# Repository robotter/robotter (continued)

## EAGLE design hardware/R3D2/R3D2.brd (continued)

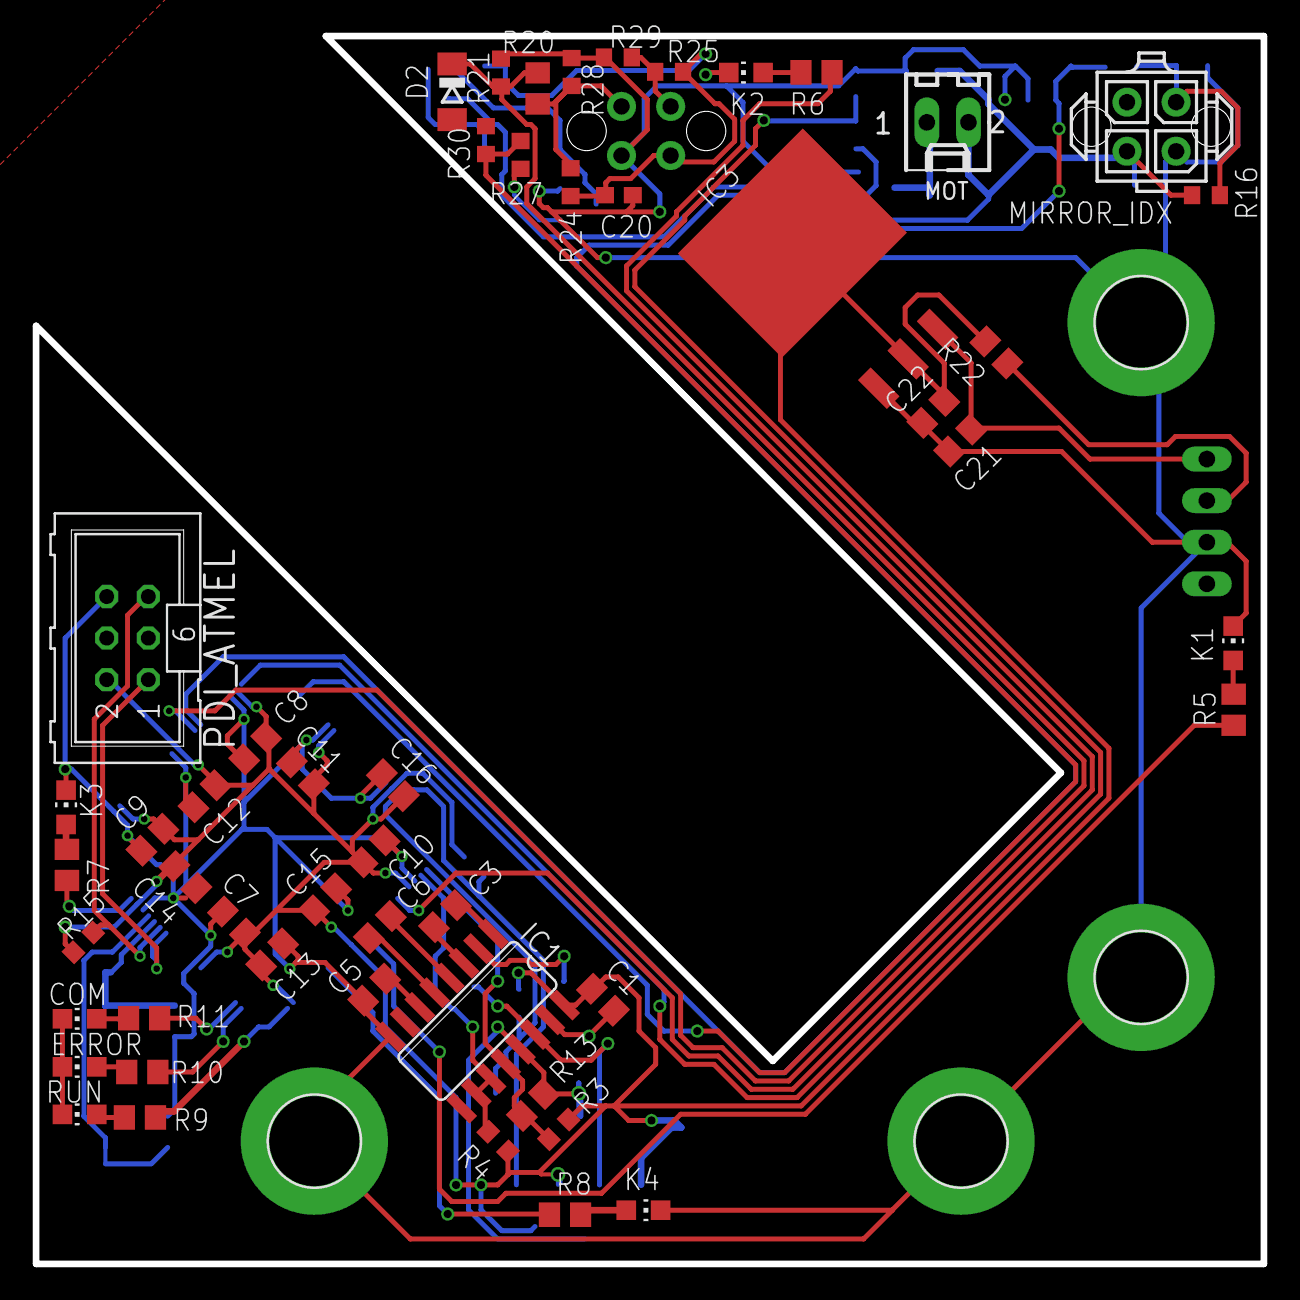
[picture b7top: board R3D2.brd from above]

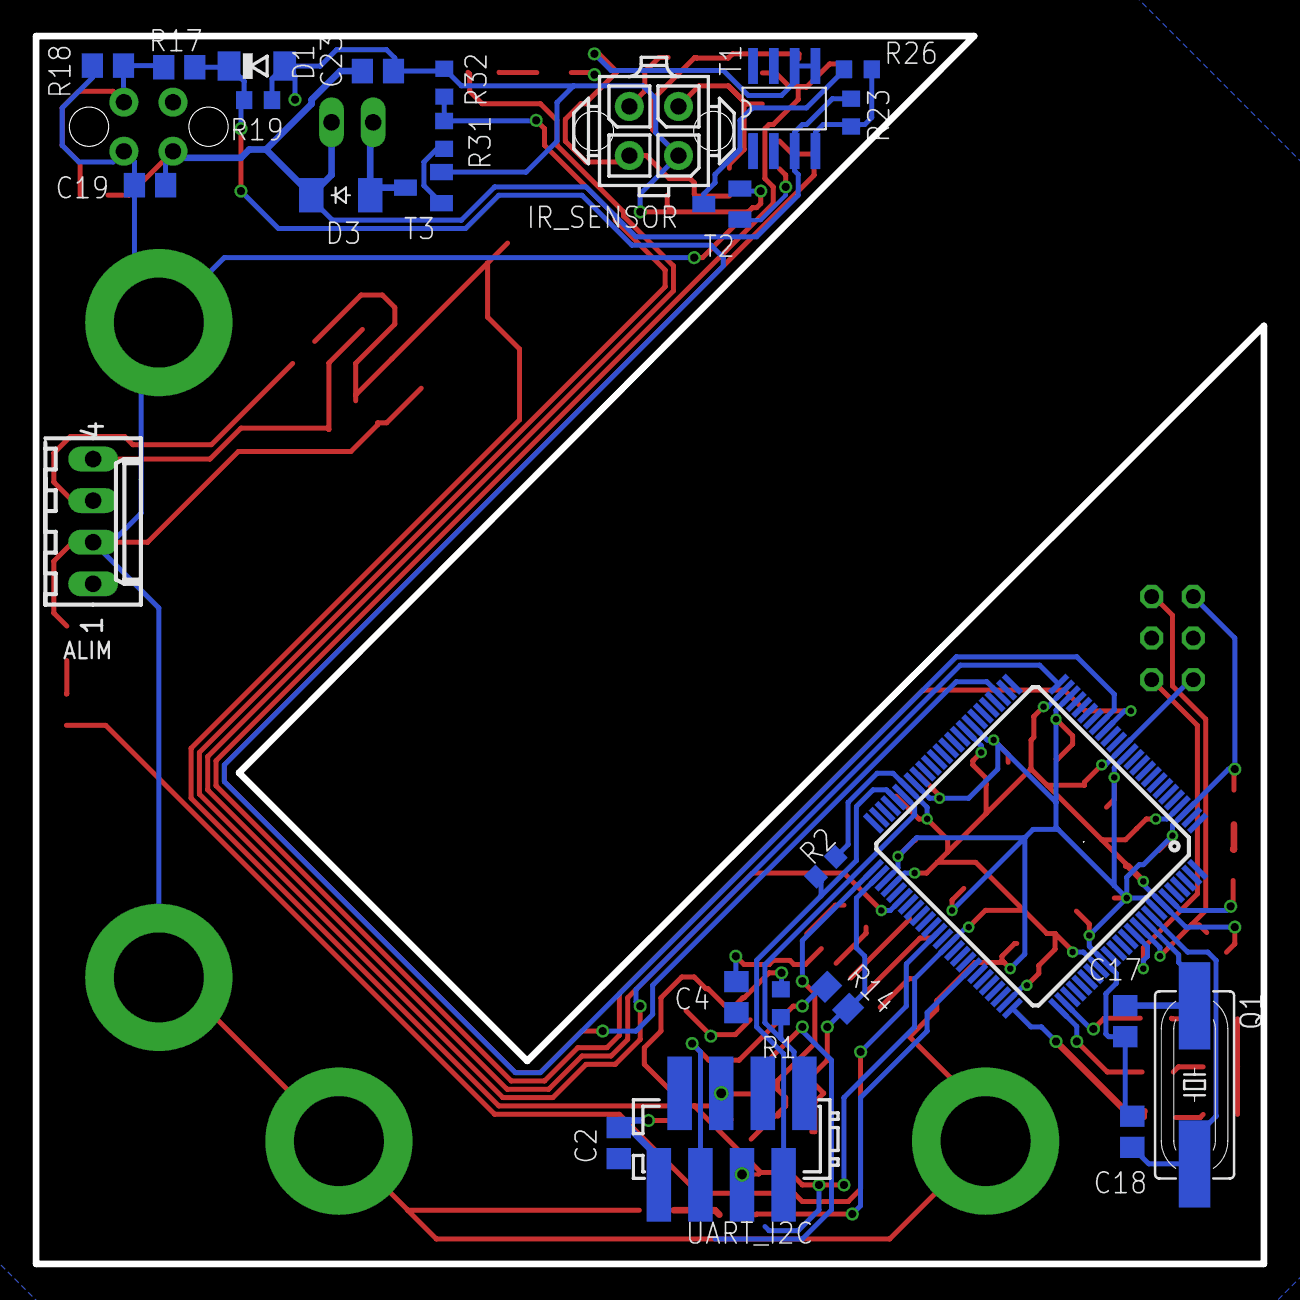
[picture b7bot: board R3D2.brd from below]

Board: 2 copper layers, 75.0 x 75.0 mm, 81 parts (26 on the bottom side), 48 nets.

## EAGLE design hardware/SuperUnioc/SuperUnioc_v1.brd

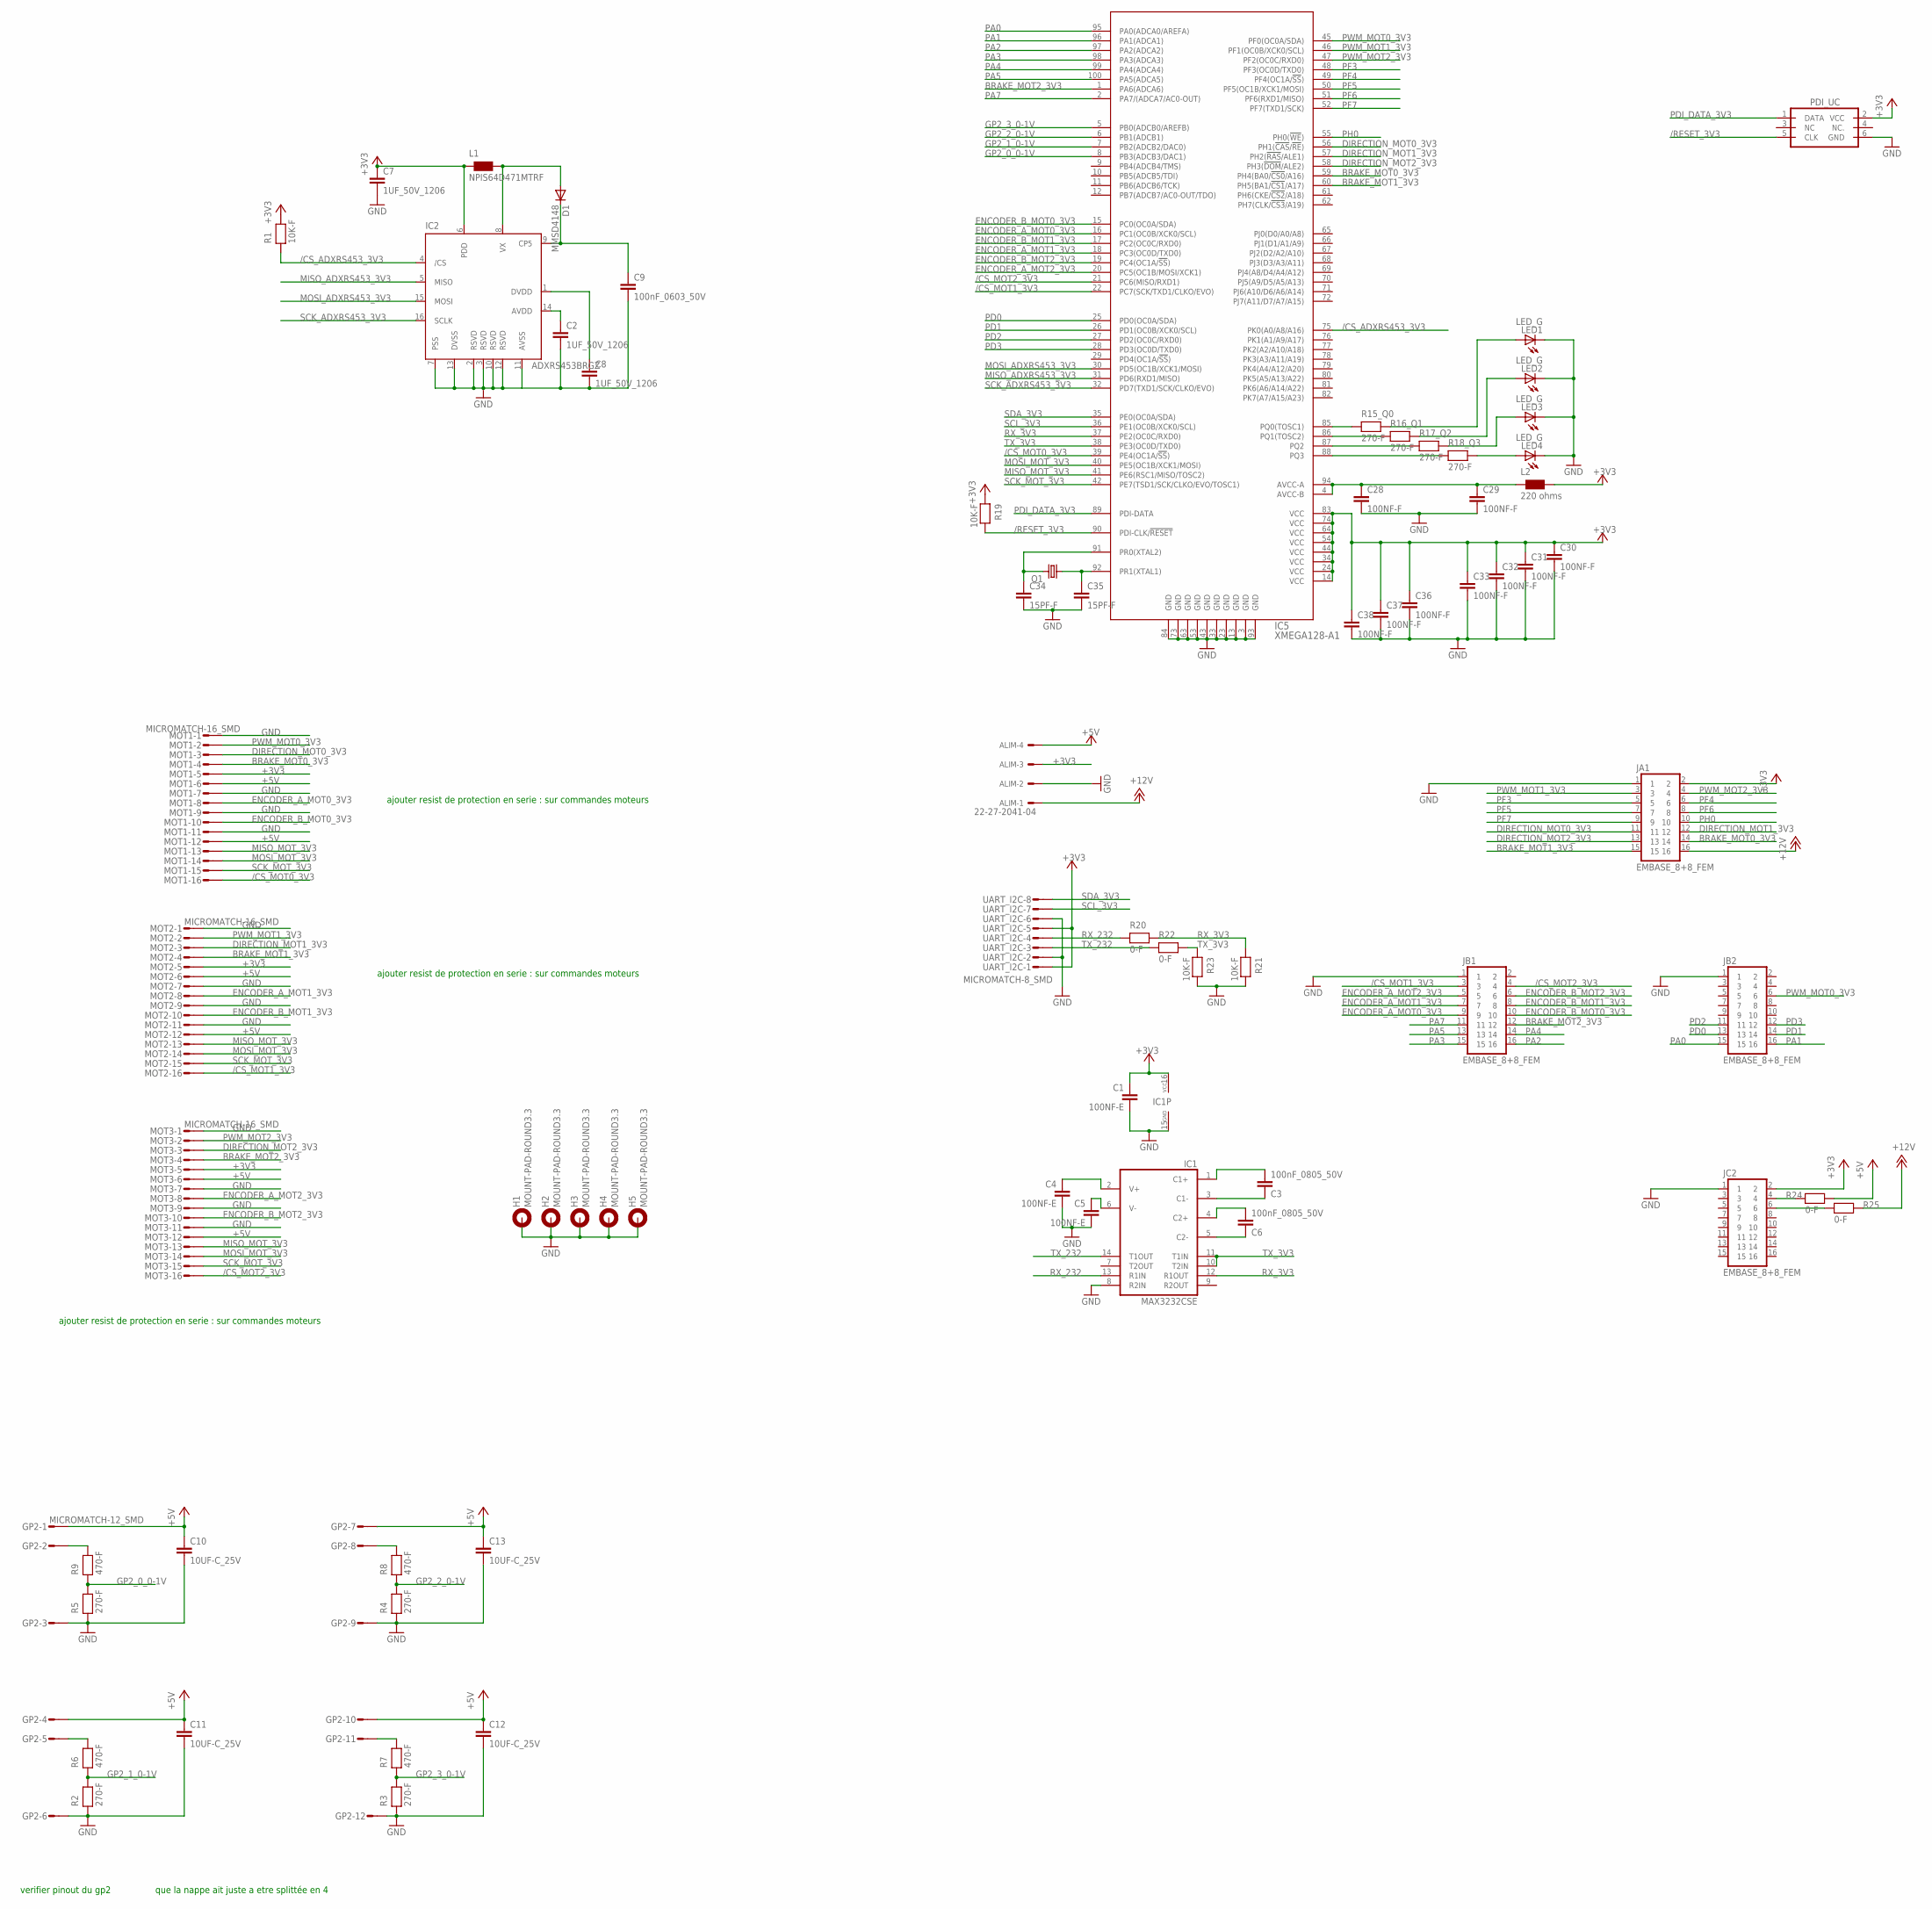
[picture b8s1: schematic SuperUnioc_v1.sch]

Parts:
ALIM: 22-27-2041-04; 6410-04
C1, C4, C5: 100NF-E; C0805
C2, C7, C8: 1UF_50V_1206; C1206
C3, C6: 100nF_0805_50V; C0805
C9: 100nF_0603_50V; C0603
C10, C11, C12, C13: 10UF-C_25V; C1210
C28, C29, C30, C31, C32, C33, C36, C37, C38: 100NF-F; C0603
C34, C35: 15PF-F; C0603
D1: MMSD4148; SOD123
GP2: MICROMATCH-12_SMD
H1, H2, H3, H4, H5: MOUNT-PAD-ROUND3.3; 3,3-PAD
IC1: MAX3232CSE; SO16
IC2: ADXRS453BRGZ; SO16_CAV
IC5: XMEGA128-A1; TQFP100
JA1: EMBASE_8+8_FEM
JB1, JB2: EMBASE_8+8_FEM
JC2: EMBASE_8+8_FEM
L1: NPIS64D471MTRF; NPSIS_D64
L2: 220 ohms; R0603
LED1, LED2, LED3, LED4: LED_G; CHIP-LED0805
MOT1, MOT2, MOT3: MICROMATCH-16_SMD
PDI_UC: PDI_ATMELL; ML6L
Q1: CRYSTAL_16MHZ_HC49UP; HC49UP
R1, R19, R21, R23: 10K-F; R0603
R2, R3, R4, R5, R15_Q0, R16_Q1, R17_Q2, R18_Q3: 270-F; R0603
R6, R7, R8, R9: 470-F; R0603
R20, R22, R24, R25: 0-F; R0603
UART_I2C: MICROMATCH-8_SMD

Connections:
+3V3: ALIM.3, C1.1, C7.1, C30.1, C31.1, C32.1, C33.1, C36.1, C37.1, C38.1, IC1.16 (VCC), IC2.6 (PDD), IC5.14 (VCC), IC5.24 (VCC), IC5.34 (VCC), IC5.44 (VCC), IC5.54 (VCC), IC5.64 (VCC), IC5.74 (VCC), IC5.83 (VCC), JA1.2, JC2.2, L1.1, L2.2, MOT1.5, MOT2.5, MOT3.5, PDI_UC.2 (VCC), R1.2, R19.1, UART_I2C.1, UART_I2C.5
+5V: ALIM.4, C10.1, C11.1, C12.1, C13.1, GP2.1, GP2.4, GP2.7, GP2.10, MOT1.6, MOT1.12, MOT2.6, MOT2.12, MOT3.6, MOT3.12, R24.2
+12V: ALIM.1, JA1.16, R25.2
/CS_ADXRS453_3V3: IC2.4 (/CS), IC5.75 (PK0(A0/A8/A16)), R1.1
/CS_MOT0_3V3: IC5.39 (PE4(OC1A/!SS!)), MOT1.16
/CS_MOT1_3V3: IC5.22 (PC7(SCK/TXD1/CLKO/EVO)), JB1.3, MOT2.16
/CS_MOT2_3V3: IC5.21 (PC6(MISO/RXD1)), JB1.4, MOT3.16
/RESET_3V3: IC5.90 (PDI-CLK/!RESET), PDI_UC.5 (CLK), R19.2
BRAKE_MOT0_3V3: IC5.59 (PH4(BA0/!CS0!/A16)), JA1.14, MOT1.4
BRAKE_MOT1_3V3: IC5.60 (PH5(BA1/!CS1!/A17)), JA1.15, MOT2.4
BRAKE_MOT2_3V3: IC5.1 (PA6(ADCA6)), JB1.12, MOT3.4
DIRECTION_MOT0_3V3: IC5.56 (PH1(!CAS!/!RE!)), JA1.11, MOT1.3
DIRECTION_MOT1_3V3: IC5.57 (PH2(!RAS!/ALE1)), JA1.12, MOT2.3
DIRECTION_MOT2_3V3: IC5.58 (PH3(!DOM!/ALE2)), JA1.13, MOT3.3
ENCODER_A_MOT0_3V3: IC5.16 (PC1(OC0B/XCK0/SCL)), JB1.9, MOT1.8
ENCODER_A_MOT1_3V3: IC5.18 (PC3(OC0D/TXD0)), JB1.7, MOT2.8
ENCODER_A_MOT2_3V3: IC5.20 (PC5(OC1B/MOSI/XCK1)), JB1.5, MOT3.8
ENCODER_B_MOT0_3V3: IC5.15 (PC0(OC0A/SDA)), JB1.10, MOT1.10
ENCODER_B_MOT1_3V3: IC5.17 (PC2(OC0C/RXD0)), JB1.8, MOT2.10
ENCODER_B_MOT2_3V3: IC5.19 (PC4(OC1A/!SS!)), JB1.6, MOT3.10
GND: ALIM.2, C1.2, C2.2, C4.2, C5.2, C7.2, C8.2, C9.2, C10.2, C11.2, C12.2, C13.2, C28.2, C29.2, C30.2, C31.2, C32.2, C33.2, C34.2, C35.2, C36.2, C37.2, C38.2, GP2.3, GP2.6, GP2.9, GP2.12, H1.B3,3, H2.B3,3, H3.B3,3, H4.B3,3, H5.B3,3, IC1.8 (R2IN), IC1.15 (GND), IC2.2 (RSVD), IC2.3 (RSVD), IC2.7 (PSS), IC2.10 (RSVD), IC2.11 (AVSS), IC2.12 (RSVD), IC2.13 (DVSS), IC5.3 (GND), IC5.13 (GND), IC5.23 (GND), IC5.33 (GND), IC5.43 (GND), IC5.53 (GND), IC5.63 (GND), IC5.73 (GND), IC5.84 (GND), IC5.93 (GND), JA1.1, JB1.1, JB2.1, JC2.1, LED1.C, LED2.C, LED3.C, LED4.C, MOT1.1, MOT1.7, MOT1.9, MOT1.11, MOT2.1, MOT2.7, MOT2.9, MOT2.11, MOT3.1, MOT3.7, MOT3.9, MOT3.11, PDI_UC.6 (GND), R2.1, R3.1, R4.1, R5.1, R21.2, R23.2, UART_I2C.2, UART_I2C.6
GP2_0_0-1V: IC5.8 (PB3(ADCB3/DAC1)), R5.2, R9.1
GP2_1_0-1V: IC5.7 (PB2(ADCB2/DAC0)), R2.2, R6.1
GP2_2_0-1V: IC5.6 (PB1(ADCB1)), R4.2, R8.1
GP2_3_0-1V: IC5.5 (PB0(ADCB0/AREFB)), R3.2, R7.1
MISO_ADXRS453_3V3: IC2.5 (MISO), IC5.31 (PD6(RXD1/MISO))
MISO_MOT_3V3: IC5.41 (PE6(RSC1/MISO/TOSC2)), MOT1.13, MOT2.13, MOT3.13
MOSI_ADXRS453_3V3: IC2.15 (MOSI), IC5.30 (PD5(OC1B/XCK1/MOSI))
MOSI_MOT_3V3: IC5.40 (PE5(OC1B/XCK1/MOSI)), MOT1.14, MOT2.14, MOT3.14
unnamed: JC2.4, R24.1
unnamed: C3.1, IC1.1 (C1+)
unnamed: C6.1, IC1.4 (C2+)
unnamed: LED4.A, R18_Q3.2
unnamed: C3.2, IC1.3 (C1-)
unnamed: IC5.88 (PQ3), R18_Q3.1
unnamed: C34.1, IC5.91 (PR0(XTAL2)), Q1.2
unnamed: C35.1, IC5.92 (PR1(XTAL1)), Q1.1
unnamed: IC5.87 (PQ2), R17_Q2.1
unnamed: IC5.86 (PQ1(TOSC2)), R16_Q1.1
unnamed: IC5.85 (PQ0(TOSC1)), R15_Q0.1
unnamed: LED1.A, R15_Q0.2
unnamed: LED2.A, R16_Q1.2
unnamed: LED3.A, R17_Q2.2
unnamed: JC2.6, R25.1
unnamed: C6.2, IC1.5 (C2-)
unnamed: C4.1, IC1.2 (V+)
unnamed: D1.A, IC2.8 (VX), L1.2
unnamed: C2.1, IC2.14 (AVDD)
unnamed: C5.1, IC1.6 (V-)
unnamed: C8.1, IC2.1 (DVDD)
unnamed: GP2.8, R8.2
unnamed: C9.1, D1.C, IC2.9 (CP5)
unnamed: GP2.2, R9.2
unnamed: C28.1, C29.1, IC5.4 (AVCC-B), IC5.94 (AVCC-A), L2.1
unnamed: GP2.11, R7.2
unnamed: GP2.5, R6.2
PA0: IC5.95 (PA0(ADCA0/AREFA)), JB2.15
PA1: IC5.96 (PA1(ADCA1)), JB2.16
PA2: IC5.97 (PA2(ADCA2)), JB1.16
PA3: IC5.98 (PA3(ADCA3)), JB1.15
PA4: IC5.99 (PA4(ADCA4)), JB1.14
PA5: IC5.100 (PA5(ADCA5)), JB1.13
PA7: IC5.2 (PA7/(ADCA7/AC0-OUT)), JB1.11
PD0: IC5.25 (PD0(OC0A/SDA)), JB2.13
PD1: IC5.26 (PD1(OC0B/XCK0/SCL)), JB2.14
PD2: IC5.27 (PD2(OC0C/RXD0)), JB2.11
PD3: IC5.28 (PD3(OC0D/TXD0)), JB2.12
PDI_DATA_3V3: IC5.89 (PDI-DATA), PDI_UC.1 (DATA)
PF3: IC5.48 (PF3(OC0D/TXD0)), JA1.5
PF4: IC5.49 (PF4(OC1A/!SS!)), JA1.6
PF5: IC5.50 (PF5(OC1B/XCK1/MOSI)), JA1.7
PF6: IC5.51 (PF6(RXD1/MISO)), JA1.8
PF7: IC5.52 (PF7(TXD1/SCK)), JA1.9
PH0: IC5.55 (PH0(!WE!)), JA1.10
PWM_MOT0_3V3: IC5.45 (PF0(OC0A/SDA)), JB2.6, MOT1.2
PWM_MOT1_3V3: IC5.46 (PF1(OC0B/XCK0/SCL)), JA1.3, MOT2.2
PWM_MOT2_3V3: IC5.47 (PF2(OC0C/RXD0)), JA1.4, MOT3.2
RX_3V3: IC1.12 (R1OUT), IC5.37 (PE2(OC0C/RXD0)), R20.2, R21.1
RX_232: IC1.13 (R1IN), R20.1, UART_I2C.4
SCK_ADXRS453_3V3: IC2.16 (SCLK), IC5.32 (PD7(TXD1/SCK/CLKO/EVO))
SCK_MOT_3V3: IC5.42 (PE7(TSD1/SCK/CLKO/EVO/TOSC1)), MOT1.15, MOT2.15, MOT3.15
SCL_3V3: IC5.36 (PE1(OC0B/XCK0/SCL)), UART_I2C.7
SDA_3V3: IC5.35 (PE0(OC0A/SDA)), UART_I2C.8
TX_3V3: IC1.10 (T2IN), IC1.11 (T1IN), IC5.38 (PE3(OC0D/TXD0)), R22.2, R23.1
TX_232: IC1.14 (T1OUT), R22.1, UART_I2C.3

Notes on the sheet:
verifier pinout du gp2
que la nappe ait juste a etre splittée en 4
ajouter resist de protection en serie : sur commandes moteurs

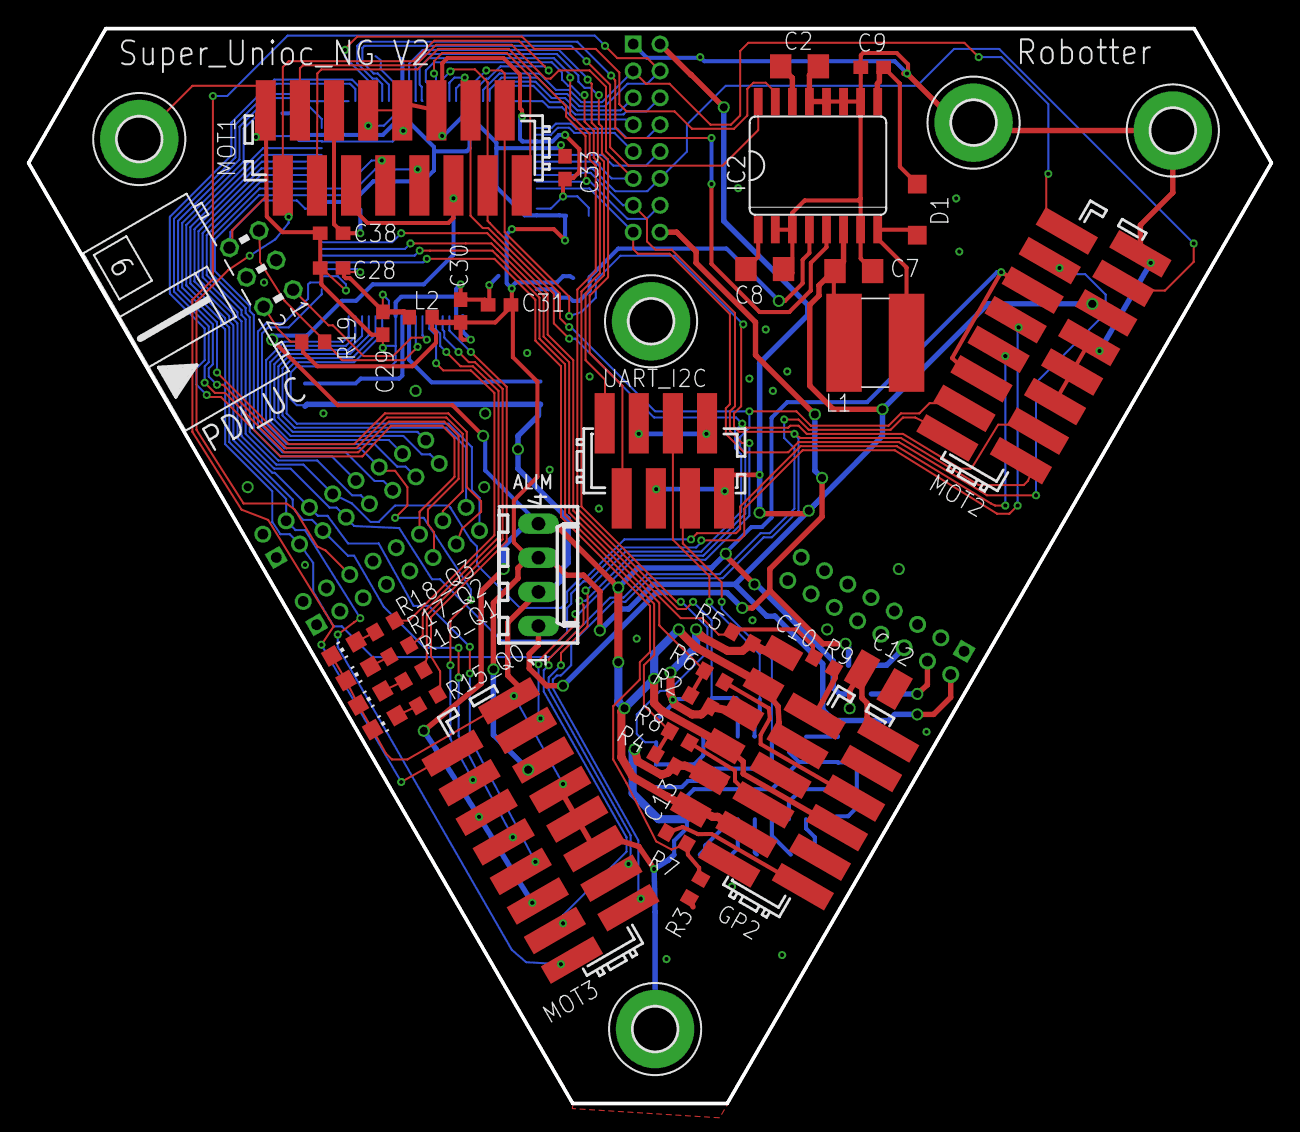
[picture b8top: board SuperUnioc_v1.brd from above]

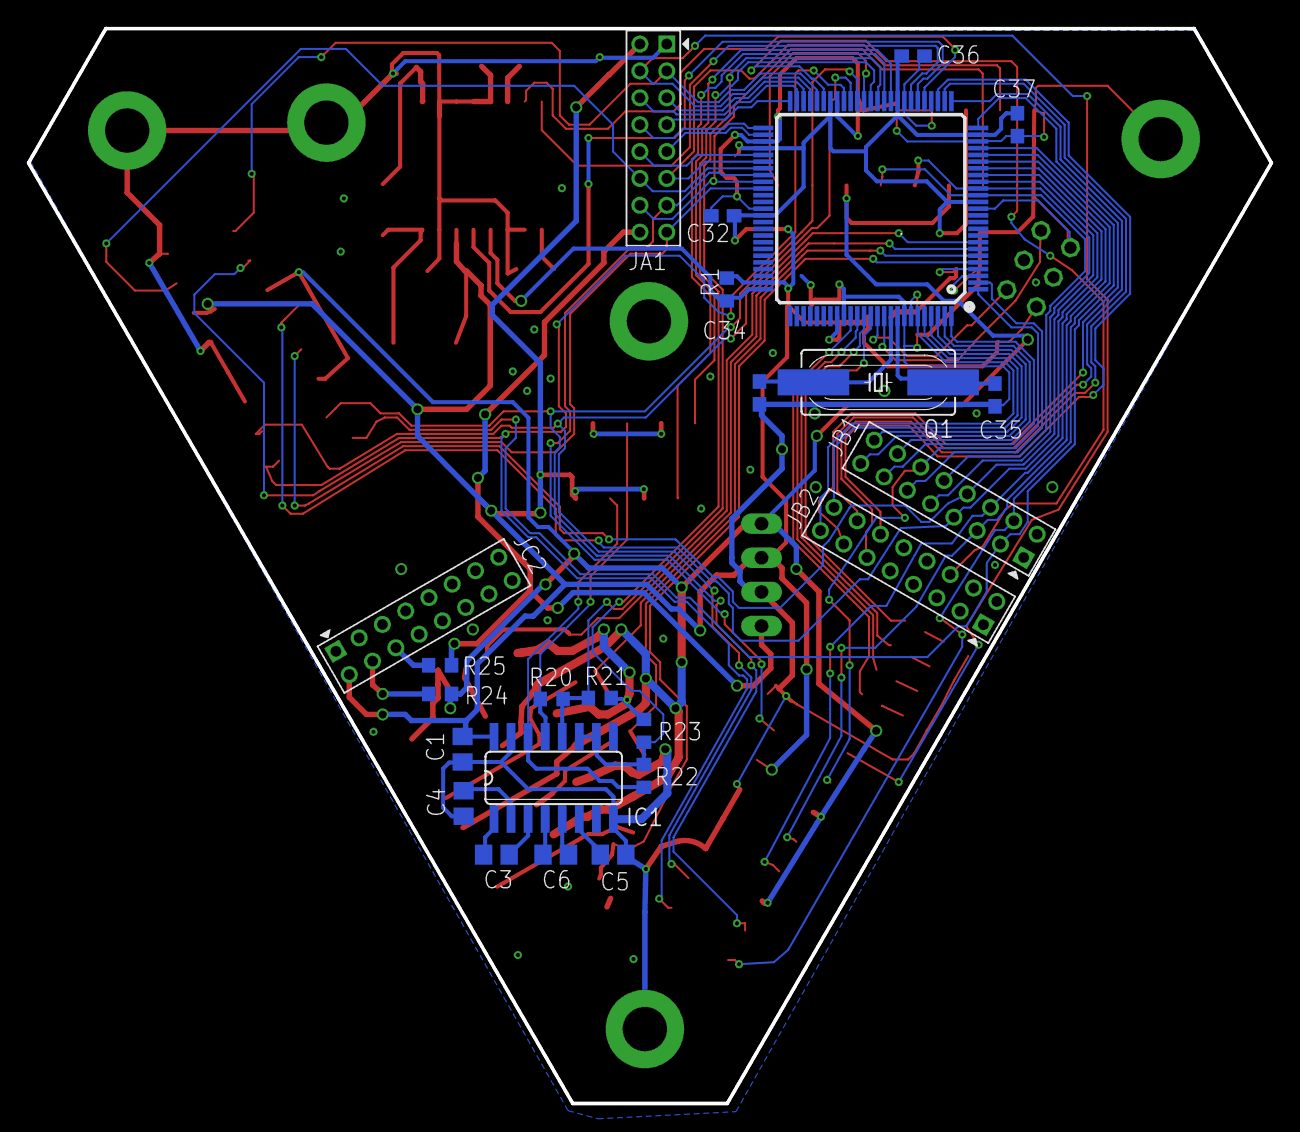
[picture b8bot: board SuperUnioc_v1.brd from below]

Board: 2 copper layers, 92.5 x 80.0 mm, 71 parts (24 on the bottom side), 85 nets.

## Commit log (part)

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2011-05-30 ASSERV: PPP handlers added
2011-05-30 PPP: support for internal commands in protocol.py
2011-05-30 PPP: new message wrapper for messages with successive mids
2011-05-30 PPP: use the new MsgGroupWrapper for Galipeur messages
2011-05-30 STRAT: first message implemention
2011-05-30 MECA: use ppp_common_callback()
2011-05-30 PPP: fixed subscribe()
2011-05-30 PPP: fixed compilation error with parameter named 'd'
2011-05-31 uart: atmega16 compatibility
2011-05-31 R3D2: project cleaning, some optimisations
2011-05-31 R3D2: dont dump filename in errors/logs
2011-05-31 R3D2: cleaning
2011-05-31 R3D2: implentation of PPP messages
2011-05-31 CLI: Bug fix on cli, uint8_t replaced by int
2011-05-31 MECA: arm release function added
2011-05-31 MECA: arm_at_pos event implemented + arm_overtorque event added
2011-05-31 ASSERV: Carrot reset added to position set
2011-05-31 MECA: bug fixed + AX12 positions modified
2011-06-01 ASSERV: autoset message modified
2011-06-01 ASSERV, MECA, R3D2, STRAT: send the 'start' event
2011-06-01 R3D2: conversions PPP values
2011-06-01 PPP: added 'arm' field to scanner_* messages
2011-06-01 R3D2: completed help messages
2011-06-01 ASSERV: autoset management added
2011-06-02 ASSERV: 90s wait time removed from code
2011-06-02 PPP: added strat messages (run, choose color)
2011-06-02 MECA/ASSERV: I2C frequency changed
2011-06-18 STRAT: fixed tirette init
2011-06-18 STRAT: homologation, first part
2011-06-18 STRAT: arm_grab() method
2011-06-18 STRAT: init, tool methods, ...
2011-06-18 STRAT: try to make it more robust
2011-06-18 STRAT: angle fixes, some glue
2011-06-18 homologation: full code, but still buggy
2011-06-18 STRAT: process overtorque when lowering arms
2011-06-18 STRAT: attempt to fix the "blocked after avoidance" bug
    Code used for 1st match
2011-06-18 STRAT: some R3D2 improvments
2011-06-18 STRAT: disable match_uart()
2011-06-18 STRAT: relative angle + other things
2011-06-18 STRAT: fixed PPP config
2011-06-18 STRAT: make sure the robot stops at the end of the match
2011-06-18 STRAT: no need to request for status in goto_a*(), now done in wait_asserv_status()
2011-06-18 STRAT: added angle offset, lower arms sooner
2011-06-18 STRAT: grabbing improvements
    Update arm_pawn_grabbed when a pawn is released on overtorque.
    Factorized the 'arm_release' wait.
2011-06-18 STRAT: add X/Y offset to compensate
2011-06-18 STRAT: more offset fixed, really lower an arm sooner
2011-06-18 STRAT: add a small turn, may help to push an hypothetic pawn
2011-06-18 STRAT: resent last angle order after avoidance, tweaked avoidance
2011-06-18 STRAT: don't use broadcasting to set the subscriber
2011-06-18 STRAT: code used for 2nd match (one more hack)
2011-09-01 some few changes on color sensor
2011-09-02 add eagle libraries
2012-02-05 DP 2012 : TODO marks removed
2012-02-05 Draft dossier tech 2012 ajouté.
2012-03-02 i2c: typo in comments
2012-03-25 bootloader: fix import error
2012-03-25 bootloader: allow to get/set baudrate on BasicSerial
    Baudrate can be get and set using the 'baudrate' property attribute.
    This is compatible with pySerial interface.
2012-04-14 calibration du robot, c'est beaucoup mieux, mais il faut encore regarder ça de près
2012-04-28 bootloader: remove I2C features, always assume UART
2012-04-28 Remove duplicate rule to build .hex file
2012-05-05 ppp: reflect IPython API changes
2012-05-05 ppp: add "transaction ID" field, to link request and responses
    This field is added to all frames and sent before the message ID.
2012-05-06 ppp: add Transaction class, improve C macros
    The Transaction class remplaces MessageWrapper and does not inherit from
    Message. A Transaction groupe one or several messages.
    From C, messages are sent using PPP_MSG_*() macros.
    Transaction-specific macros are also:
    - PPP_SEND_*() and PPP_REPLY_*() for commands
    - PPP_SEND_*() for orders and events
2012-05-06 ppp: complete binding rewrite
2012-05-08 update Hreidmarr : board sent to manufacturer, eagle lib used for coke and super unioc
2012-05-14 ppp: ensure compatibility with Aversive UART module
2012-05-14 uart: fix "integer overflow" warning in baudrate configuration
2012-05-14 ppp: fix strict-aliasing warning
2012-05-14 prop: board is now silent, ready for ppp.
2012-05-14 ppp: update messages for Galipeur (first step)
2012-05-14 prop: PPP update, use RobOtter UART module
2012-05-14 uart: fix disable TX (not working though), and compile error
2012-05-14 r3d2: add new PPP messages
2012-05-14 r3d2: update PPP config, disable I2C
2012-05-14 r3d2: implement new PPP orders and commands
2012-05-15 meca: add setting to disable UART UI
2012-05-15 meca: reenable Aversive UART module
2012-05-15 meca: remove/updated deprecated stuff from 2011
    Remove code for scanners and ground detectors.
    Update arm handling.
2012-05-15 meca: don't update PPP in UART UI mode, send PPP start
2012-05-15 meca: allow to manually set brush speed
2012-05-15 meca: set calibrated values for arm positions
2012-05-16 meca: retrieve brush position
2012-05-16 meca: implement "kill" order, add method to stop AX12s
2012-05-16 unioc_asserv: Unwanted NOTICE from imu rx removed
2012-05-16 unioc_asserv : Avoidance "force" added to PPP messages.
2012-05-16 ppp: process_input() return True if something has been processed
2012-05-16 ppp: Orders are now Commands, to have a hack
    Receiving a ACK even for orders is important to avoid flooding atmega's
    UARTs.
2012-05-16 r3d2: 'disappeared' message added to r3d2
    Disappeared is sent when R3D2 no longer detect a robot.
2012-05-16 unioc_asserv : ADNSBOOT is now overrided. ADNS go to hell.
2012-05-17 ppp: add binding method to process all pending input
2012-05-17 meca: arm speed parameter added to PPP messages
2012-05-18 prop: fix set steering/cruise speed PPP messages
2012-12-09 New PPP version, major changes
    Rob'Otter specific messages will be handled in the ROOM payload.
    Files for source generation have moved to avarix.
2012-12-09 ppp: add hub implementation with base features
2012-12-23 ppp: fix variable renaming
2013-01-19 ppp: fix and improve ROOM parameter casting for pack/unpack
2013-01-20 DOC : fix typo from previous commit
2013-04-06 add R3D2_v2 board, atmega 16 becomes Atxmega128A1
2013-04-06 add meca 2k13 v1 board
2013-04-06 add motor control board for principal robot
2013-04-13 ppp: fix disconnection detection in hub
    epoll() will trigger one EPOLLIN event per received data chunk.
    If data is split into two successive chunks, the whole data is read when
    processing the first EPOLLIN and no data will be received for a second
    one, which is considered as a disconnection.
2013-04-25 ppp: room: deduce packsize from packfmt, and use it in unpack()
2013-04-25 ppp: room: fix typo in previous commit
2013-04-27 ppp: fix disconnection detection
    Disconnection may lead to an infinite loop, a EPOLLIN being triggered
    indefinitely for the disconnected client.
    Also allow to call stop() from the polling thread.
2013-05-01 bugfix, baudrate forced to 38400 in perlimpinpin.io
2013-05-05 ppp: don't abort Hub on Frame formatting error
2013-05-05 ppp: initialize response attribute on PayloadRoom
2013-05-06 ppp: allow to schedule callbacks in the hub
2013-05-07 ppp: add a flag to enable/disable frame printing in HubClient
2013-05-19 Hardware:add power board that drive arm cc motors
2013-05-19 hardware: add pmi extension board v1
2013-05-19 hardware: R3D2: rename R3D2_V2 in R3D2
2013-09-29 add sabotter board \n add micro mat'n lok connector horizontal 2*2v
2013-10-03 add audio amplifier
2013-10-13 board ready for eirbot assembly, sabotter V1
2013-10-20 SuperUnioc v2 : add gyroscope ADXRS453 to board, removed FPGA
2013-10-23 led inverted, now in ascending order
2013-11-13 sabotter: uart modified after Jdam peer review
2013-12-09 add radiospares part number in eagle libraries
2013-12-10 add 3,3v and 5v regulator
2013-12-12 photointerrupter added to board, interfaces added, regulator added
2013-12-12 add color_proximity_sensor board
2013-12-27 microcontroler added
2013-12-27 sabotter/sabotter.sch
    footprint correction
2013-12-27 correction after Damien review
2013-12-27 added super unioc extension for analog servo
2013-12-27 milling deleted on some connectors
2013-12-27 milling deleted on usb and audio connector
2014-01-03 pdi connector added
2014-01-03 added dual bc847 transistor component
2014-01-03 board routed
2014-01-03 traces modified
2014-02-02 rome: add callback for sent frames
    This will allows subclasses to log not only received frames but sent frames as
    well.
2014-02-08 eagle lib modified
2014-02-08 add meca_2014 board
2014-02-09 rome: check message IDs, prevent use of ID 0 (reserved)
2014-02-26 MECA 2014 : fixes to brd
2014-02-27 eagle library update
2014-03-04 modified switch dpdt
2014-03-05 power supply rerouted, board ready to be sent to manufacturer
2014-03-08 add 100 ohms resistos
2014-03-08 ir index polarization resistor value changed after Damien review of prism_idx_suport board
2014-03-17 few changes on board
2014-03-17 add gerber pannel tools
2014-03-17 add pannel script for color_proximity_sensor board
2014-03-28 add mouser references
2014-04-01 mouser ref modified
2014-04-08 added SN75ALS193 and HEDL554x encoder connector
2014-04-19 add adp3331 regulator
2014-04-25 diameter of via increased
2014-05-28 prism v2 : modifications after beacon integration : mirror motor supplied by vbat or +15V, diode B160 pinout corrected
2014-05-28 text added
2014-05-28 SuperUnioc/SuperUnioc_v1.brd
    mouser ref added
2014-05-29 rome: make ClientEcho available in rome.client module
2014-06-11 corrected adxrs footprint
2014-09-29 rome: add a method to unregister messages
2014-10-27 rome: remove garbage comments
2014-10-27 rome: fix a comment
2014-12-06 rome: minor types rework to prepare for additional types
    Define a new (sub)metaclass for fixed-size types.
2014-12-07 rome: add a class for fixed-size array types
2014-12-19 rome: handle case of variable-length messages
2014-12-20 rome: add enum type, based on uint8
2015-01-25 IRF7205PBF added
2015-01-26 DP2015 : premier brouillon
2015-01-26 DP2015 : fix + lien youtube
2015-02-08 rome: fix misnamings in client for (try_* -> retry_*)
2015-05-09 rome: allow to define types in message definitions
    This is convenient to define common types near messages that use them
    and without embedding the type definition in the message definition.
2015-08-02 components addes in eagle libs
2015-08-02 R3D2_long_range added : sch finished, brd on work !
2015-08-08 routing board and remarks taken into account in sch
2015-08-08 board V1 routed
2015-08-09 com led moved to be viewable with others debug leds
2016-01-12 eaglelibs: robot wiring wip
2016-01-31 galiper wirring : some connectors added, WIP
2016-01-31 galiper wirring : meca board added, need to update board version and final meca wirring
2016-02-01 hardware : add BOM of RS order, some libs need to be updated
2016-02-06 components oreder nb for RS and FARNELL updated
2016-05-03 rome: add 'device' parameter to bootloader order
2016-05-03 rome: add built-in messages for bootloader
2016-05-03 rome: make FourCC a fixed type
2016-05-11 Remove perlimpinpin code (obsolete)
2018-03-30 Improve Python3 compatibility, fix minor bugs
    Generation works with Python3. Client has not been tested.
2018-04-18 Fix Python3 packing/unpacking of rome strings
2018-04-19 Add a 'bytes' type for binary strings, use it for bootloader
2018-04-28 color_proximity_sensor : VL53L0X sensor integrated
2018-04-28 R3D2_long_range : some comments added
2018-04-28 sabotter : cosmetic changes
2018-05-13 rome: properly check message and parameter names
    - Prevent of names prefixed by '_'.
    - Avoid errors when instanciating frames with parameters named 'msg' or
    'self' (the first one was used for logs).
